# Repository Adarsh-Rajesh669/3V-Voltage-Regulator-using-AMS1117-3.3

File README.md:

# 3.3V-Voltage-Regulator-using-AMS1117-3.3
A basic 3.3V voltage regulator using the AMS1117-3.3 linear voltage regulator IC. It converts an unregulated DC input into a stable 3.3V output, ideal for powering microcontrollers like esp8266 nodemcu , esp32 and other electronic compoents

Components Used :
AMS1117-3.3 Voltage Regulator IC

Input Capacitor: 10 µF

Output Capacitor: 22 µF

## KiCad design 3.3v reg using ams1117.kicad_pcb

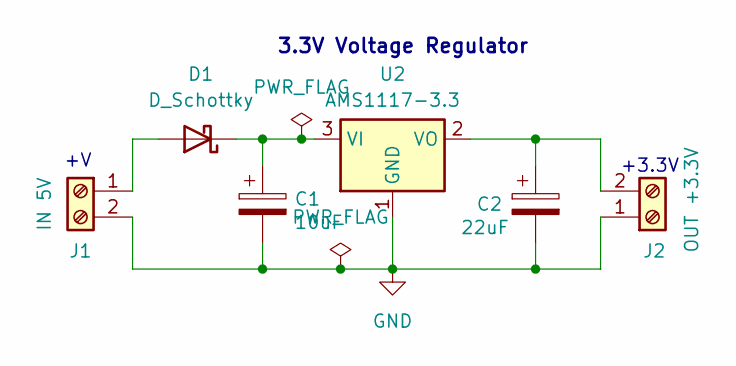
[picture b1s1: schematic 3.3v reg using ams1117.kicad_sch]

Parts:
C1: 10uF; CP_Radial_D5.0mm_P2.50mm
C2: 22uF; CP_Radial_D5.0mm_P2.50mm
D1: D_Schottky; D_0805_2012Metric
J1: IN 5V; TerminalBlock_bornier-2_P5.08mm
J2: OUT +3.3V; TerminalBlock_bornier-2_P5.08mm
U2: AMS1117-3.3; SOT-223-3_TabPin2

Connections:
GND: C1.2, C2.2, J1.2, J2.1, U2.1 (GND)
unnamed: D1.2 (A), J1.1
unnamed: C1.1, D1.1 (K), U2.3 (VI)
unnamed: C2.1, J2.2, U2.2 (VO)

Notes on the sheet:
+3.3V
3.3V Voltage Regulator

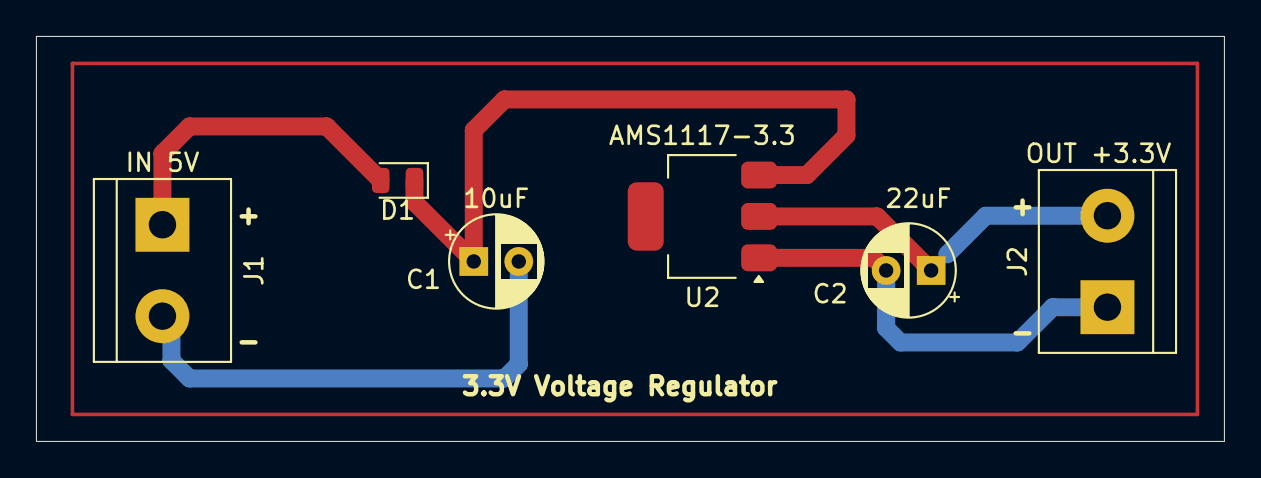
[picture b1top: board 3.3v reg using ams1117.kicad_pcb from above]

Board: 2 copper layers, 66.0 x 22.5 mm, 6 parts (0 on the bottom side), 4 nets.
